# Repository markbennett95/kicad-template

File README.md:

# Weather Man Overdrive

KiCAD files for the Weather Man overdrive - our flagship overdrive pedal. Various versions of it can be viewed by pulling the right version number. Finalized version numbers are detailed below:

## v1.1.0-build
Weather man mkI, revB PCB. 
 - Gain, volume, voice, and treble controls. More akin to the classic KoT or BB schematics. 
 - Suitable for use in 1590BB dual OD custom builds, or in a 1590B enclosure.
 - Uses legacy imperial 4-pot hole spacing, as in documentation on google drive. 

## v2.0.0-build
Weather man mkII, rev A PCB - "Grant Version"
 - First pass of the WMII, has separate bass/treble controls, still has voice knob, and external clipping switch.
 - Designed for 125B/1590N
 - Uses custom layout, labelled Weather Man mkII revA Layout on google drive

## v2.1.0-build
Weather man mkII, rev D PCB
 - Updated version of WMII from Nov 2019, voice switch and internal clipping switches
 - Designed for 125B/1590N
 - Uses legacy imperial 5 pot, 1 toggle, 2 footSW layout

## v2.1.1-build
Weather man mkII, first serialized PCB
 - Updated with presence control, board-mounted jacks, and connections for ribbon cables
 - Designed for 125B/1590N
 - Switched from 2N5458 JFET's to MMBFJ201 SMD JFETs - had no choice, stock is unavailable
 - Uses standard metric 5 pot, 1 toggle, 2 footSW layout, saved on tayda site

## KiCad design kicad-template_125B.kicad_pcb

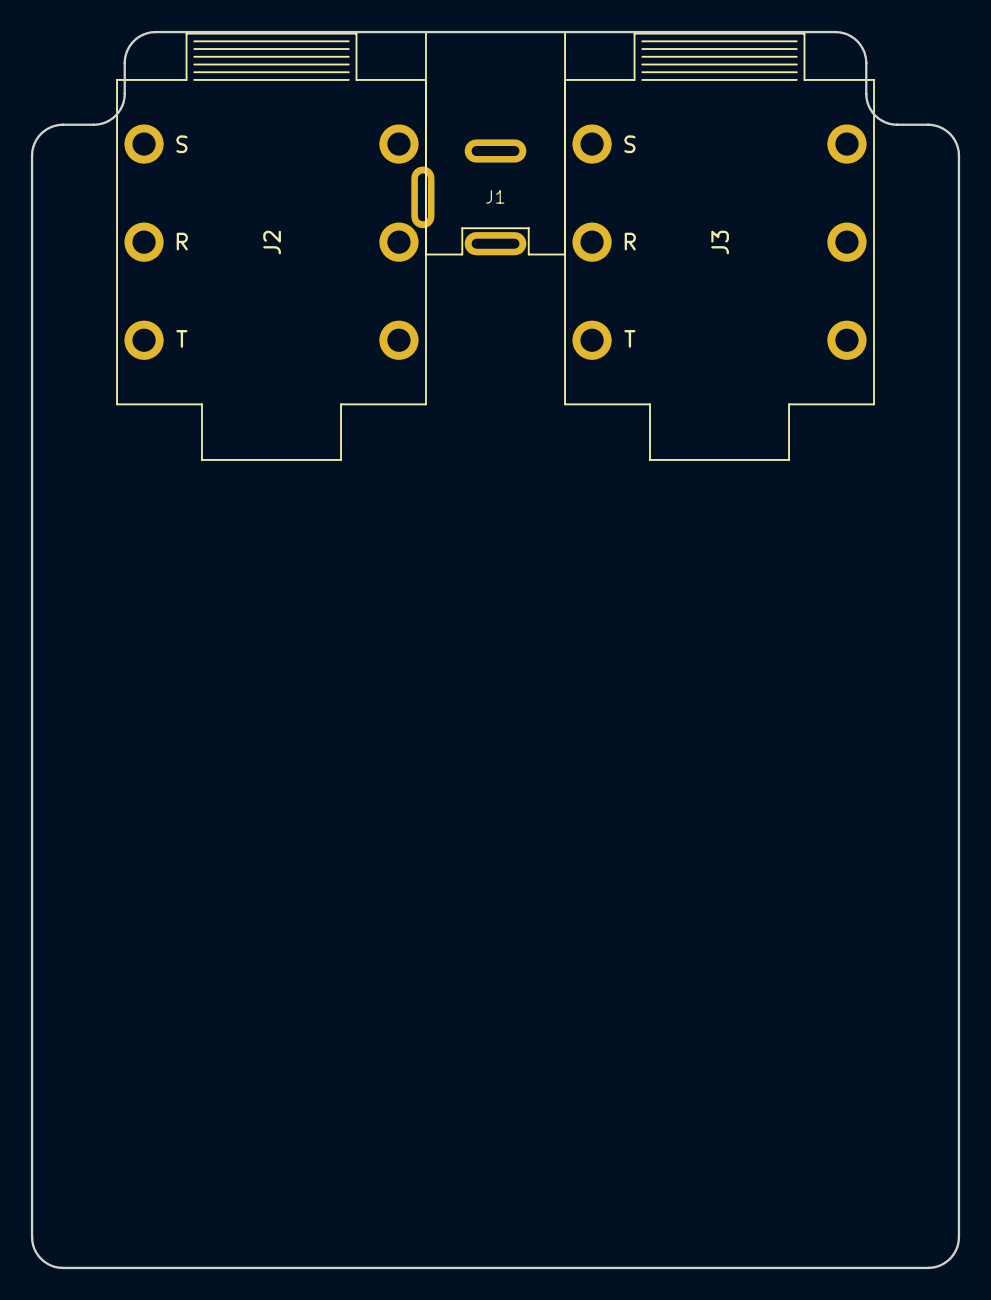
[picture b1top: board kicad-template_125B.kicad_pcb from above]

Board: 2 copper layers, 60.0 x 80.0 mm, 3 parts (0 on the bottom side), 2 nets, no tracks yet.

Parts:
J1: Barrel_Jack_Switch; DC_Jack_DC005
J2, J3: AudioJack_TRS; Rean_NYS215

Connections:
Earth: J2.3, J2.4, J2.6, J3.2, J3.3, J3.4, J3.5, J3.6
unnamed: J1.1, J2.2

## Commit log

2022-04-29 added readme, .gitignore, and kicadproject
2022-04-29 added second template PCB file
2022-04-29 updated 1590BB layout to landscape
2022-04-29 Added jacks to schematic, filetted 125B PCB
